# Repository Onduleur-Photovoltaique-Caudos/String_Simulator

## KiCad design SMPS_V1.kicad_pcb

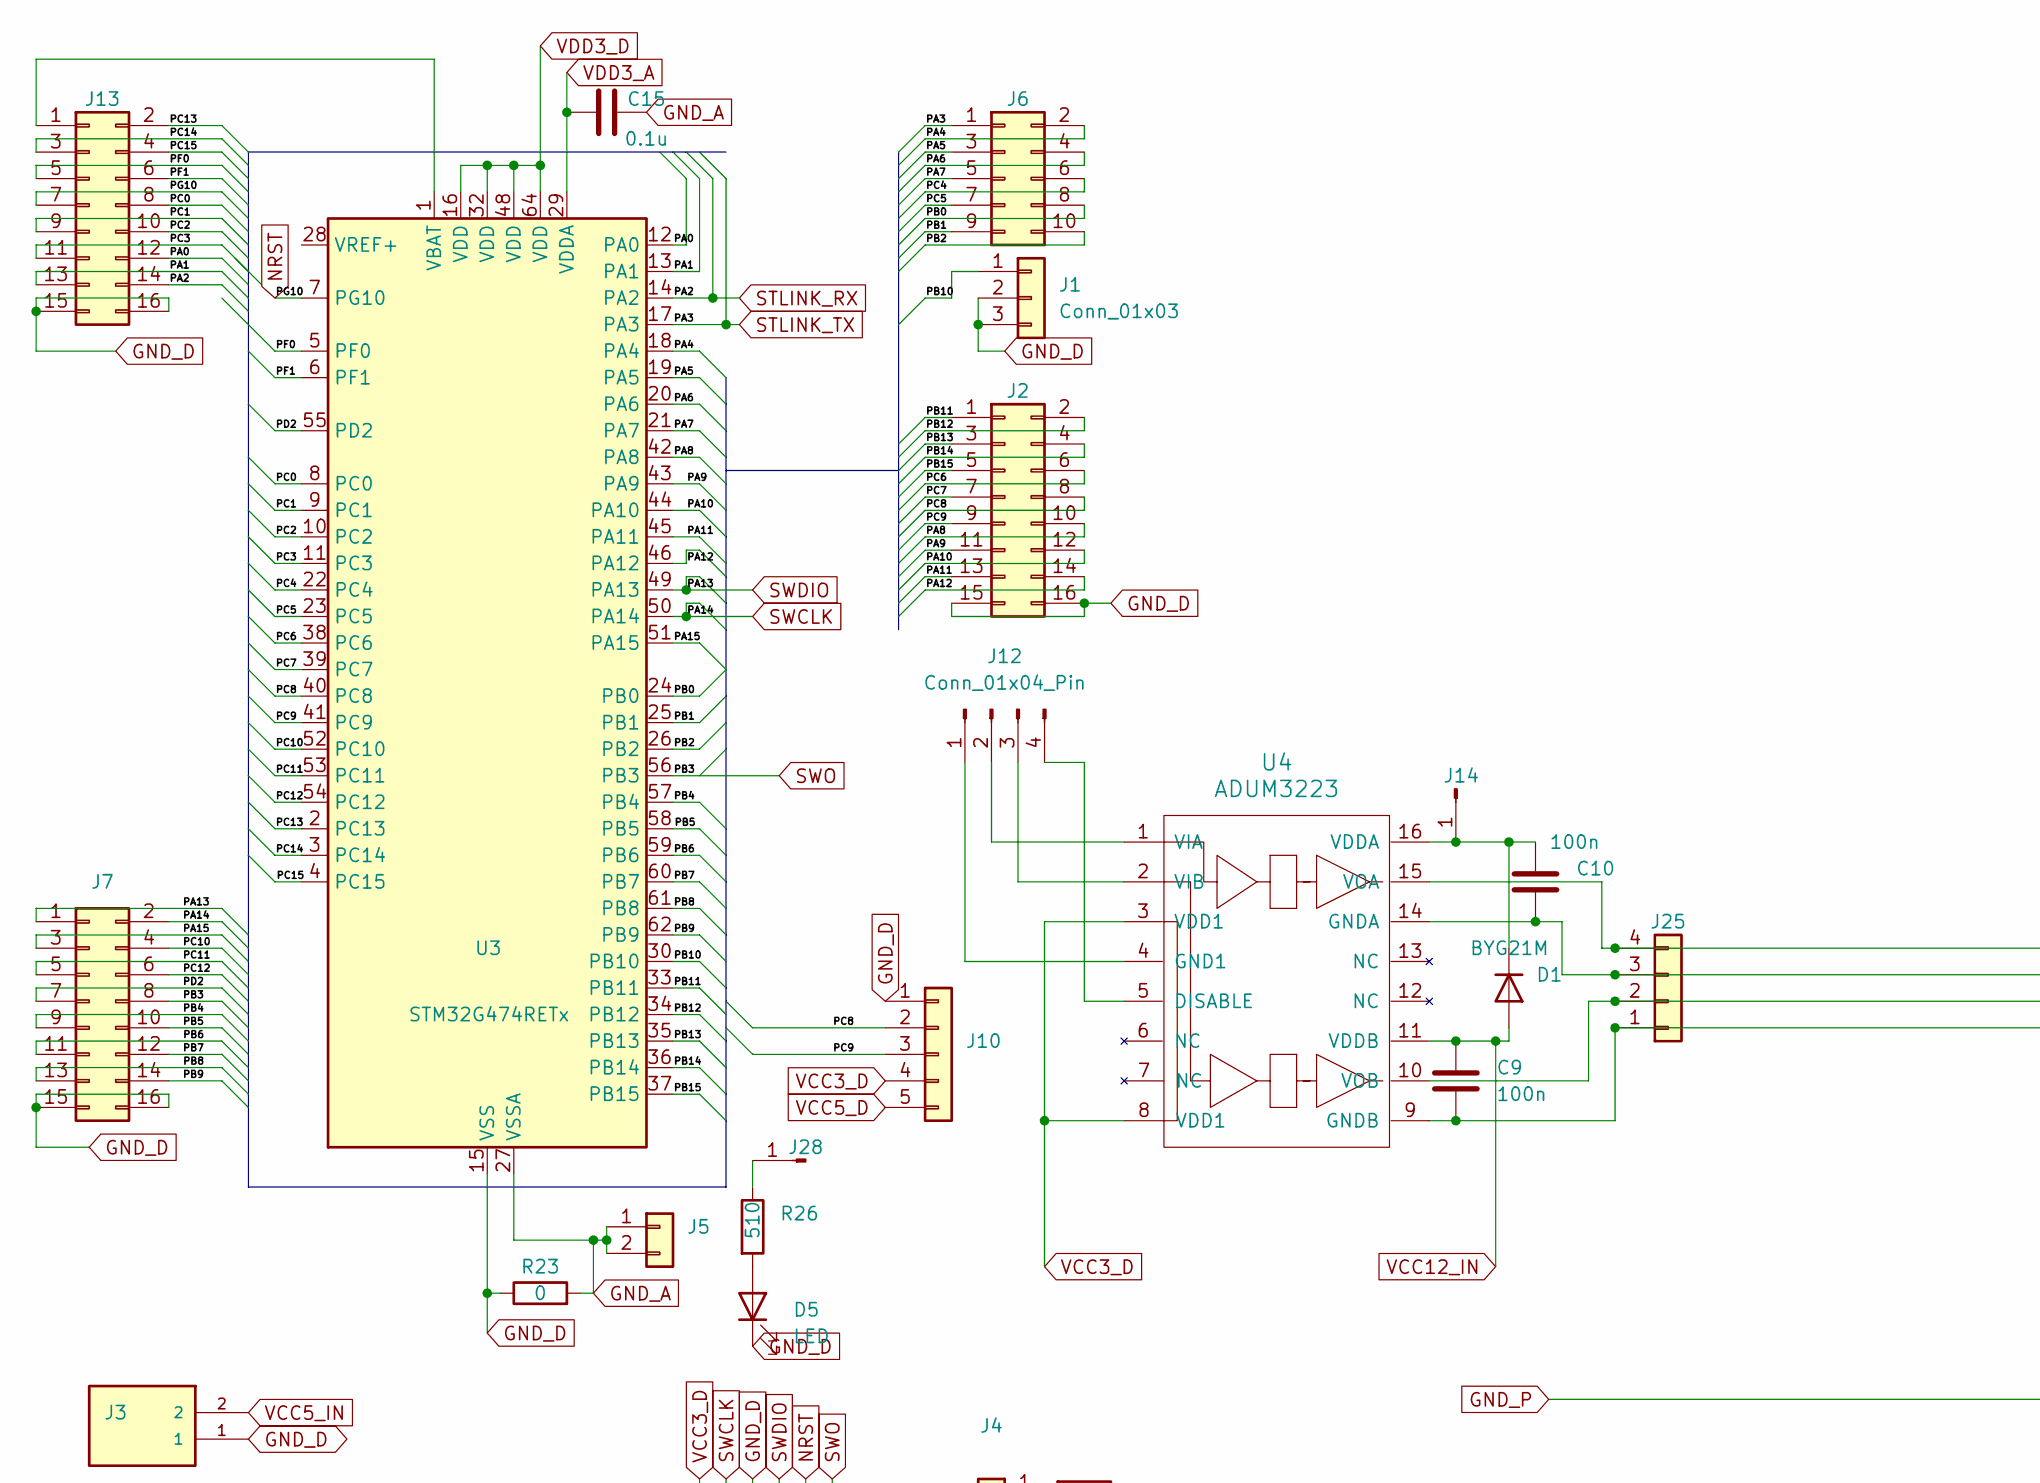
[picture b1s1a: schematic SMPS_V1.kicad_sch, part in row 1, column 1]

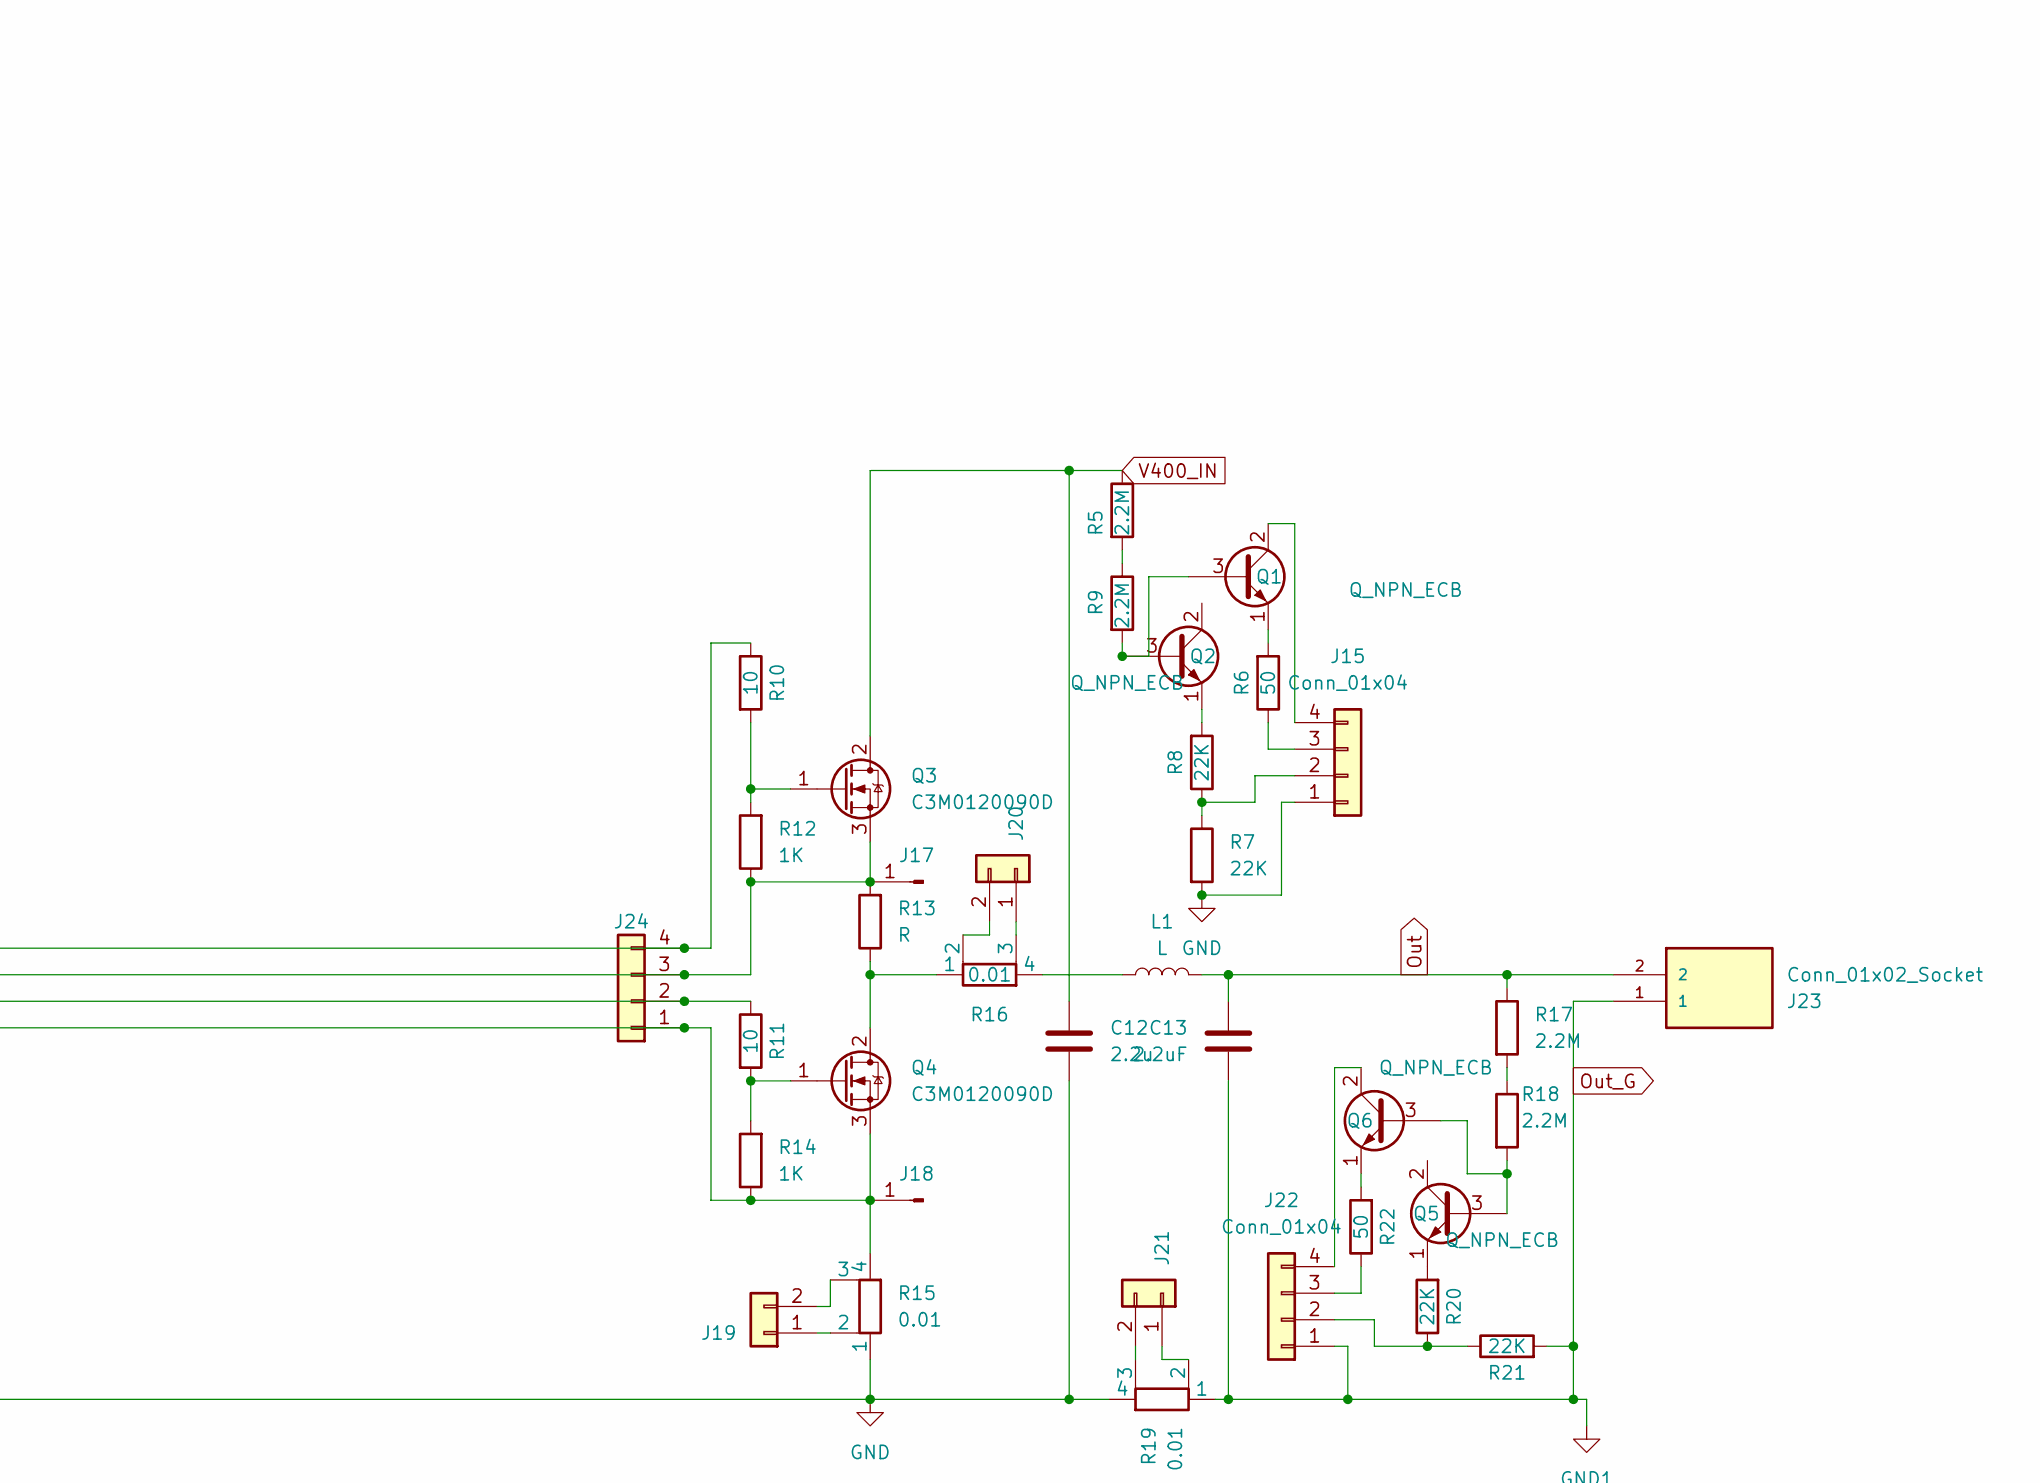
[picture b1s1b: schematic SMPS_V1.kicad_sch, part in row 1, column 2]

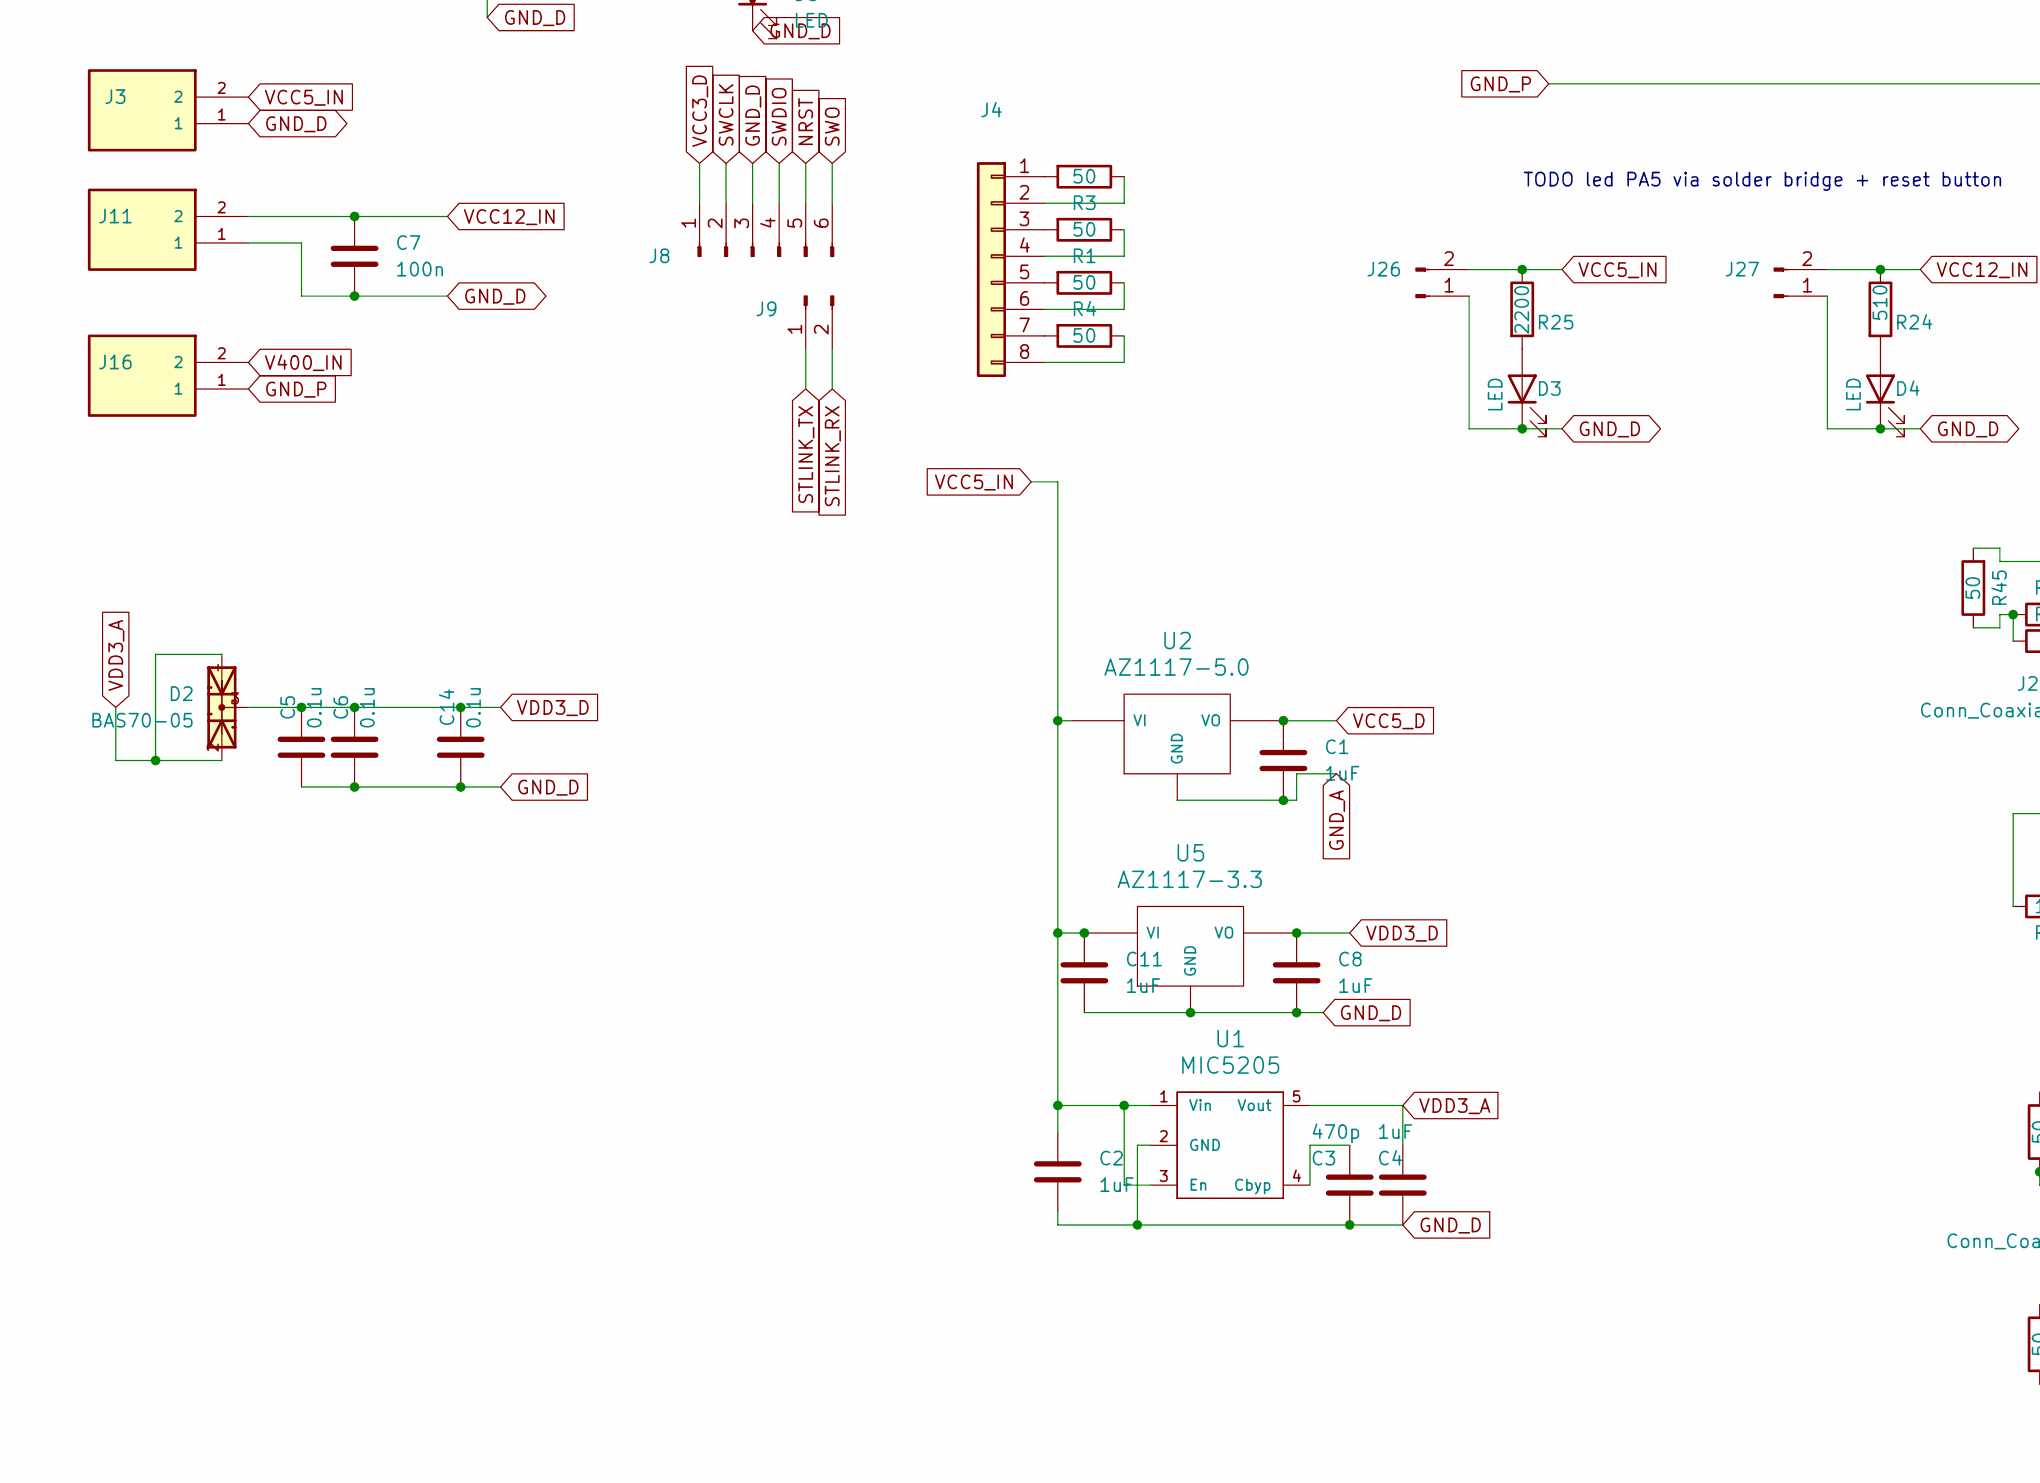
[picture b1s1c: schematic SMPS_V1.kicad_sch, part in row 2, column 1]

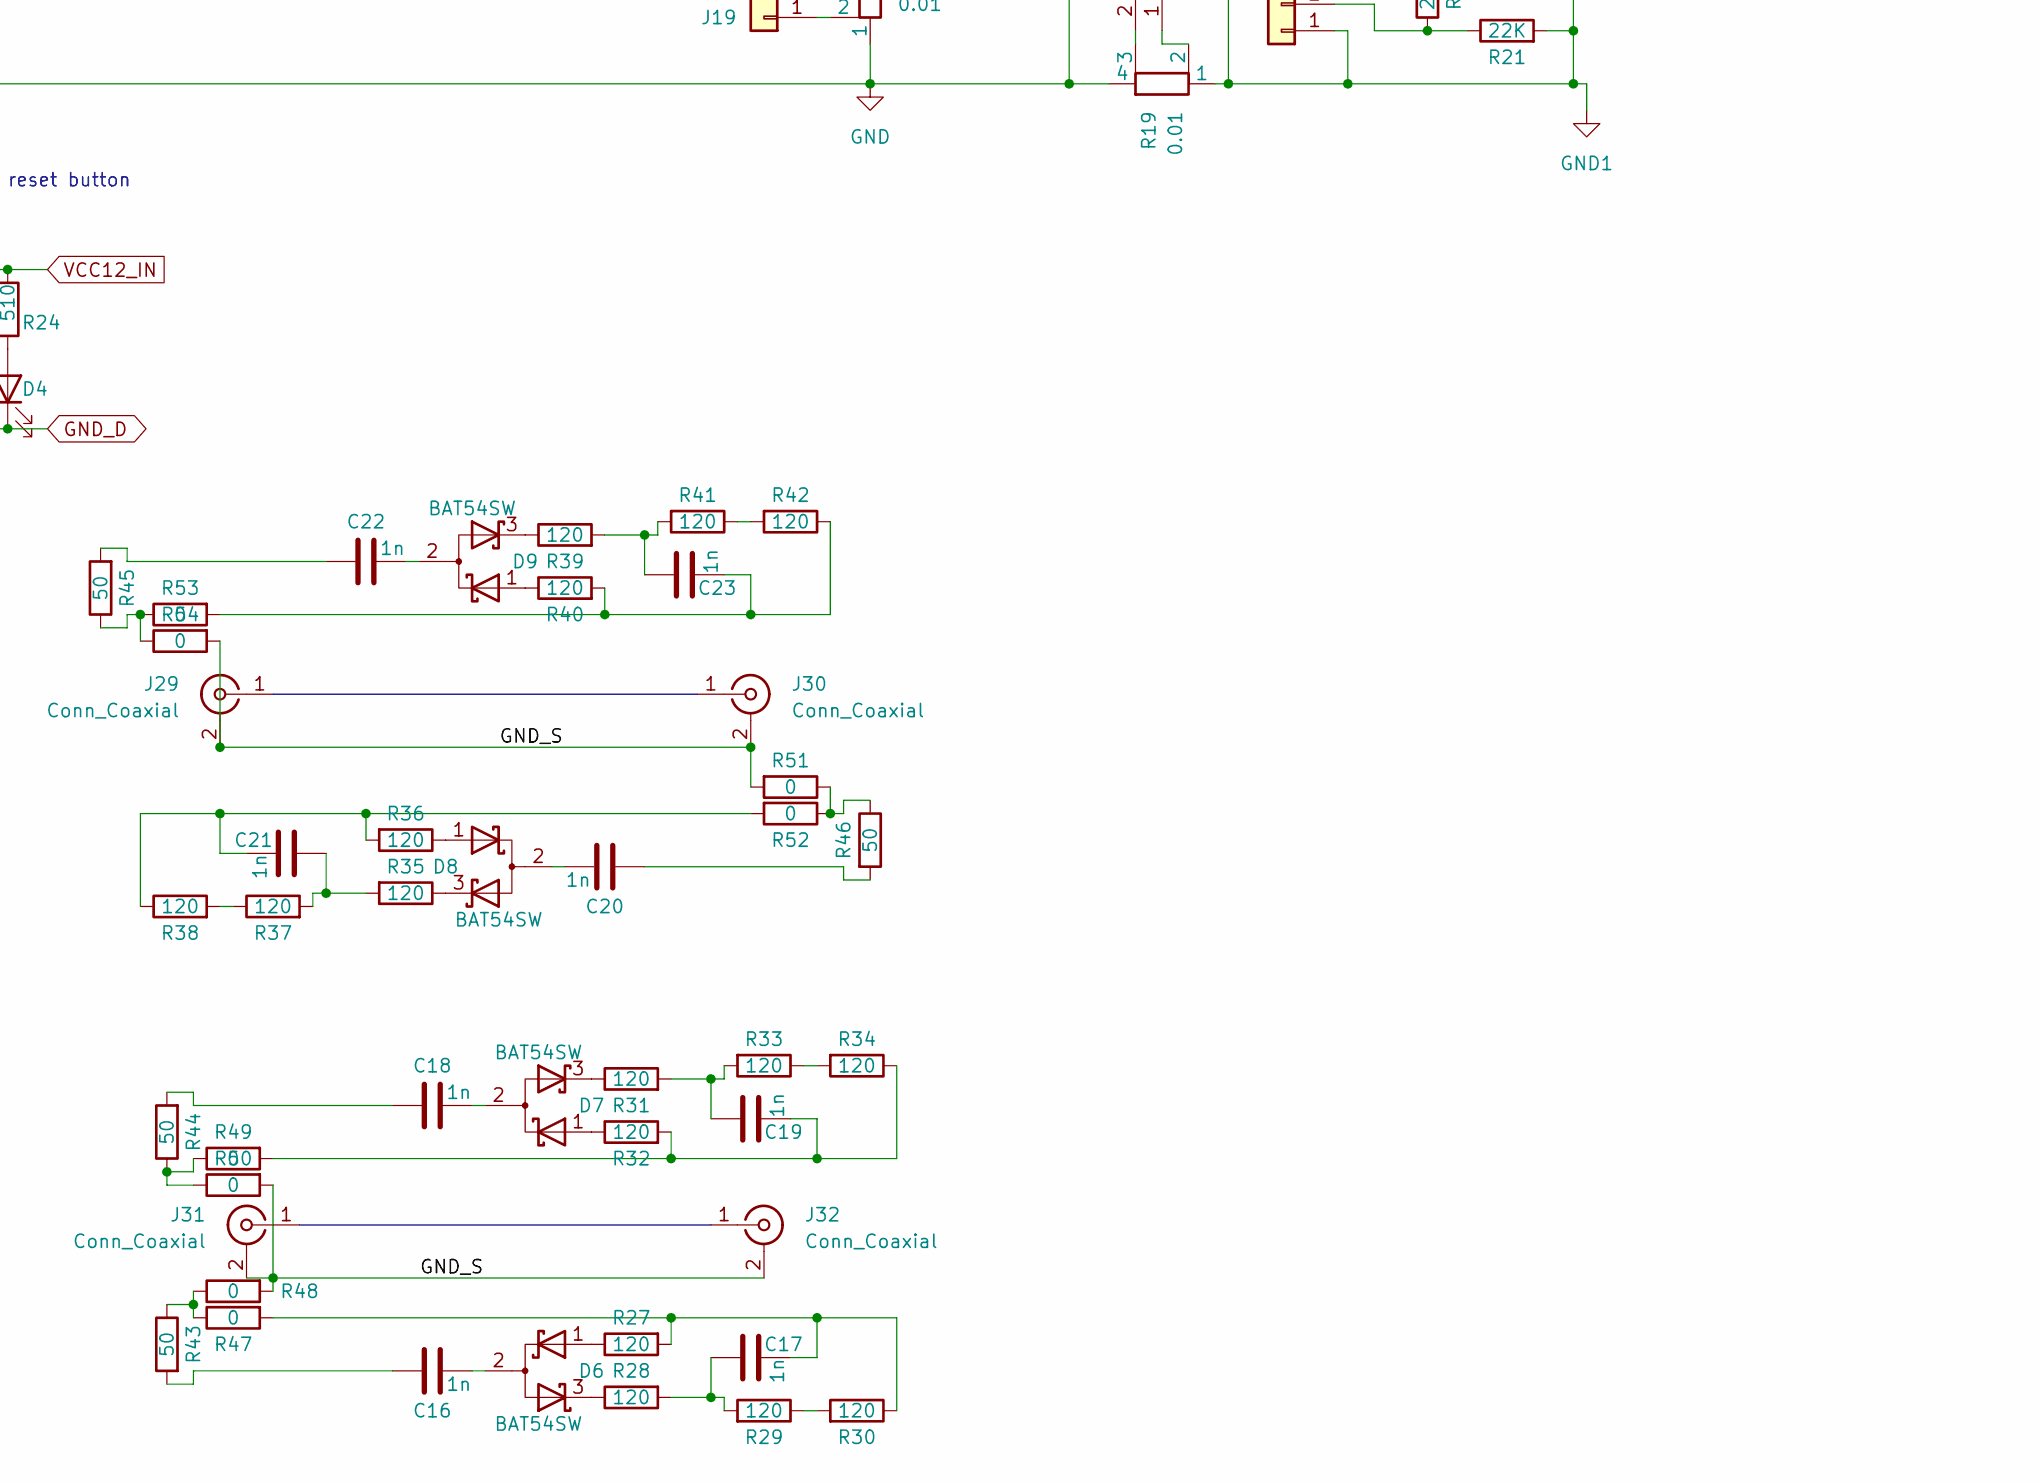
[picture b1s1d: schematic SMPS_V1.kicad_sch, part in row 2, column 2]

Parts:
C1: 1uF; LED_0805_2012Metric
C2, C4, C8, C11: 1uF; C_0603_1608Metric
C3: 470p; C_0603_1608Metric
C5, C6, C14, C15: 0.1u; C_0603_1608Metric
C7, C9, C10: 100n; C_1206_3216Metric
C12: 2.2u; C_Rect_W15_L32_P27.5
C13: 2.2uF; C_Rect_W15_L32_P27.5
C16, C17, C18, C19, C20, C21, C22, C23: 1n; C_0603_1608Metric
D1: BYG21M; DO-214-AC_SMA
D2: BAS70-05; SOT23
D3, D4, D5: LED; LED_0805_2012Metric
D6, D7, D8, D9: BAT54SW; SOT-23-D-PP
J1: Conn_01x03; PinHeader_1x03_P2.54mm_Vertical
J2, J7, J13: Conn_02x08_Odd_Even; PinHeader_2x08_P2.54mm_Vertical
J3, J11, J16, J23: Conn_01x02_Socket; CUI_TB004-508-P02BE
J4: Conn_01x08; PinHeader_1x08_P2.54mm_Vertical
J5, J19, J20, J21: Conn_01x02; PinHeader_1x02_P2.54mm_Vertical
J6: Conn_02x05_Odd_Even; PinHeader_2x05_P2.54mm_Vertical
J8: Conn_01x06_Pin; PinSocket_1x06_P2.54mm_Vertical
J9: Conn_01x02_Pin; PinSocket_1x02_P2.54mm_Vertical
J10: Conn_01x05; PinHeader_1x05_P2.54mm_Vertical
J12: Conn_01x04_Pin; PinHeader_1x04_P2.54mm_Vertical
J14, J17, J18, J28: Conn_01x01_Pin; PinHeader_1x01_P2.54mm_Vertical
J15, J22, J25: Conn_01x04; PinHeader_1x04_P2.54mm_Vertical
J24: Conn_01x04; PinSocket_1x04_P2.54mm_Vertical
J26, J27: Conn_01x02_Pin; PinHeader_1x02_P2.54mm_Vertical
J29, J30, J31, J32: Conn_Coaxial; SMA_Molex_73251-1153_EdgeMount_Horizontal
L1: L; Toroid-44-22
Q1, Q2, Q5, Q6: Q_NPN_ECB; SOT-23
Q3, Q4: C3M0120090D; TO-247-3_Vertical
R1, R2, R3, R4, R6, R22, R43, R44, R45, R46: 50; R_0603_1608Metric
R5, R9, R17, R18: 2.2M; R_1206_3216Metric_Pad1.30x1.75mm_HandSolder
R7, R8, R20, R21: 22K; R_0603_1608Metric
R10, R11: 10; R_0603_1608Metric
R12, R14: 1K; R_0603_1608Metric
R13: R; R_Axial_DIN0614_L14.3mm_D5.7mm_P15.24mm_Horizontal
R15, R16, R19: 0.01; R_Shunt_Axial_DIN0414_L11.9mm_D4.5mm_P15.24mm_Horizontal
R23, R47, R48, R49, R50, R51, R52, R53, R54: 0; R_0603_1608Metric
R24, R26: 510; R_0603_1608Metric
R25: 2200; R_0603_1608Metric
R27, R28, R29, R30, R31, R32, R33, R34, R35, R36, R37, R38, R39, R40, R41, R42: 120; R_0603_1608Metric
U1: MIC5205; SOT23-5
U2: AZ1117-5.0; SOT-223
U3: STM32G474RETx; LQFP-64_10x10mm_P0.5mm
U4: ADUM3223; SOIC-16_3.9x9.9mm_P1.27mm
U5: AZ1117-3.3; SOT-223

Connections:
/GND_S: J29.2 (Ext), J30.2 (Ext), J31.2 (Ext), J32.2 (Ext), R48.2, R50.2, R51.2, R54.2
/PA0: J13.12, U3.12 (PA0)
/PA1: J13.13, U3.13 (PA1)
/PA4: J6.2, U3.18 (PA4)
/PA5: J6.3, U3.19 (PA5)
/PA6: J6.4, U3.20 (PA6)
/PA7: J6.5, U3.21 (PA7)
/PA8: J2.10, U3.42 (PA8)
/PA9: J2.11, U3.43 (PA9)
/PA10: J2.12, U3.44 (PA10)
/PA11: J2.13, U3.45 (PA11)
/PA12: J2.14, U3.46 (PA12)
/PA15: J7.3, U3.51 (PA15)
/PB0: J6.8, U3.24 (PB0)
/PB1: J6.9, U3.25 (PB1)
/PB2: J6.10, U3.26 (PB2)
/PB4: J7.9, U3.57 (PB4)
/PB5: J7.10, U3.58 (PB5)
/PB6: J7.11, U3.59 (PB6)
/PB7: J7.12, U3.60 (PB7)
/PB8: J7.13, U3.61 (PB8)
/PB9: J7.14, U3.62 (PB9)
/PB10: J1.1, U3.30 (PB10)
/PB11: J2.1, U3.33 (PB11)
/PB12: J2.2, U3.34 (PB12)
/PB13: J2.3, U3.35 (PB13)
/PB14: J2.4, U3.36 (PB14)
/PB15: J2.5, U3.37 (PB15)
/PC0: J13.8, U3.8 (PC0)
/PC1: J13.9, U3.9 (PC1)
/PC2: J13.10, U3.10 (PC2)
/PC3: J13.11, U3.11 (PC3)
/PC4: J6.6, U3.22 (PC4)
/PC5: J6.7, U3.23 (PC5)
/PC6: J2.6, U3.38 (PC6)
/PC7: J2.7, U3.39 (PC7)
/PC8: J2.8, J10.2, U3.40 (PC8)
/PC9: J2.9, J10.3, U3.41 (PC9)
/PC10: J7.4, U3.52 (PC10)
/PC11: J7.5, U3.53 (PC11)
/PC12: J7.6, U3.54 (PC12)
/PC13: J13.2, U3.2 (PC13)
/PC14: J13.3, U3.3 (PC14)
/PC15: J13.4, U3.4 (PC15)
/PD2: J7.7, U3.55 (PD2)
/PF0: J13.5, U3.5 (PF0)
/PF1: J13.6, U3.6 (PF1)
GND_A: C1.2, C15.2, J5.1, J5.2, R23.2, U2.1 (GND), U3.27 (VSSA)
GND_D: C2.2, C3.2, C4.2, C5.1, C6.1, C7.2, C8.2, C11.2, C14.1, D3.1 (K), D4.1 (K), D5.1 (K), J1.2, J1.3, J2.15, J2.16, J3.1, J7.15, J7.16, J8.3, J10.1, J11.1, J13.15, J13.16, J26.1, J27.1, R23.1, U1.2 (GND), U3.15 (VSS), U3.31 (VSS), U3.47 (VSS), U3.63 (VSS), U5.1 (GND)
GND_P: C12.2, J15.1, J16.1, R7.2, R15.1, R19.4
NRST: J8.5, J13.7, U3.7 (PG10)
unnamed: C16.1, R43.2
unnamed: C17.1, R27.2, R30.1, R47.2
unnamed: C17.2, R28.2, R29.2
unnamed: C18.1, R44.2
unnamed: C19.1, R32.2, R34.1, R49.2
unnamed: C19.2, R31.2, R33.2
unnamed: C20.1, R46.2
unnamed: C21.1, R36.2, R38.1, R52.2
unnamed: C21.2, R35.2, R37.2
unnamed: C22.1, R45.2
unnamed: C23.1, R40.2, R42.1, R53.2
unnamed: C23.2, R39.2, R41.2
unnamed: C10.1, D1.1 (K), J14.1, U4.16 (VDDA)
unnamed: D3.2 (A), R25.2
unnamed: D4.2 (A), R24.2
unnamed: D5.2 (A), R26.2
unnamed: C16.2, D6.2 (A)
unnamed: D6.1 (K), R27.1
unnamed: D6.3 (K), R28.1
unnamed: C18.2, D7.2 (A)
unnamed: D7.1 (K), R32.1
unnamed: D7.3 (K), R31.1
unnamed: C20.2, D8.2 (A)
unnamed: D8.1 (K), R36.1
unnamed: D8.3 (K), R35.1
unnamed: C22.2, D9.2 (A)
unnamed: D9.1 (K), R40.1
unnamed: D9.3 (K), R39.1
unnamed: J4.1, R2.2
unnamed: J4.2, R2.1
unnamed: J4.3, R3.2
unnamed: J4.4, R3.1
unnamed: J4.5, R1.2
unnamed: J4.6, R1.1
unnamed: J4.7, R4.2
unnamed: J4.8, R4.1
unnamed: J12.1, U4.4 (GND1)
unnamed: J12.2, U4.1 (VIA)
unnamed: J12.3, U4.2 (VIB)
unnamed: J12.4, U4.5 (DISABLE)
unnamed: J13.1, U3.1 (VBAT)
unnamed: J15.2, R7.1, R8.1
unnamed: J15.3, R6.1
unnamed: J15.4, Q1.2 (C)
unnamed: C10.2, J17.1, J24.3, J25.3, Q3.3 (S), R12.1, R13.2, U4.14 (GNDA)
unnamed: C9.2, J18.1, J24.1, J25.1, Q4.3 (S), R14.1, R15.4, U4.9 (GNDB)
unnamed: J19.1, R15.2
unnamed: J19.2, R15.3
unnamed: J20.1, R16.3
unnamed: J20.2, R16.2
unnamed: J21.1, R19.2
unnamed: J21.2, R19.3
unnamed: J22.2, R20.1, R21.1
unnamed: J22.3, R22.1
unnamed: J22.4, Q6.2 (C)
unnamed: J24.2, J25.2, R11.1, U4.10 (VOB)
unnamed: J24.4, J25.4, R10.1, U4.15 (VOA)
unnamed: J28.1, R26.1
unnamed: J29.1 (In), J30.1 (In)
unnamed: J31.1 (In), J32.1 (In)
unnamed: L1.1, R16.4
unnamed: Q1.3 (B), Q2.3 (B), R9.2
unnamed: Q1.1 (E), R6.2
unnamed: Q2.1 (E), R8.2
unnamed: Q3.1 (G), R10.2, R12.2
unnamed: Q4.2 (D), R13.1, R16.1
unnamed: Q4.1 (G), R11.2, R14.2
unnamed: Q5.3 (B), Q6.3 (B), R18.2
unnamed: Q5.1 (E), R20.2
unnamed: Q6.1 (E), R22.2
unnamed: R5.2, R9.1
unnamed: R17.2, R18.1
unnamed: R29.1, R30.2
unnamed: R33.1, R34.2
unnamed: R37.1, R38.2
unnamed: R41.1, R42.2
unnamed: R43.1, R47.1, R48.1
unnamed: R44.1, R49.1, R50.1
unnamed: R45.1, R53.1, R54.1
unnamed: R46.1, R51.1, R52.1
unnamed: C3.1, U1.4 (Cbyp)
Out: C13.1, J23.2, L1.2, R17.1
Out_G: C13.2, J22.1, J23.1, R19.1, R21.2
STLINK_RX: J9.2, J13.14, U3.14 (PA2)
STLINK_TX: J6.1, J9.1, U3.17 (PA3)
SWCLK: J7.2, J8.2, U3.50 (PA14)
SWDIO: J7.1, J8.4, U3.49 (PA13)
SWO: J7.8, J8.6, U3.56 (PB3)
V400_IN: C12.1, J16.2, Q3.2 (D), R5.1
VCC3_D: J8.1, J10.4, U4.3 (VDD1), U4.8 (VDD1)
VCC5_D: C1.1, J10.5, U2.2 (VO)
VCC5_IN: C2.1, C11.1, J3.2, J26.2, R25.1, U1.1 (Vin), U1.3 (En), U2.3 (VI), U5.3 (VI)
VCC12_IN: C7.1, C9.1, D1.2 (A), J11.2, J27.2, R24.1, U4.11 (VDDB)
VDD3_A: C4.1, C15.1, D2.1, D2.2, U1.5 (Vout), U3.29 (VDDA)
VDD3_D: C5.2, C6.2, C8.1, C14.2, D2.3, U3.16 (VDD), U3.32 (VDD), U3.48 (VDD), U3.64 (VDD), U5.2 (VO)

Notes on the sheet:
TODO led PA5 via solder bridge + reset button

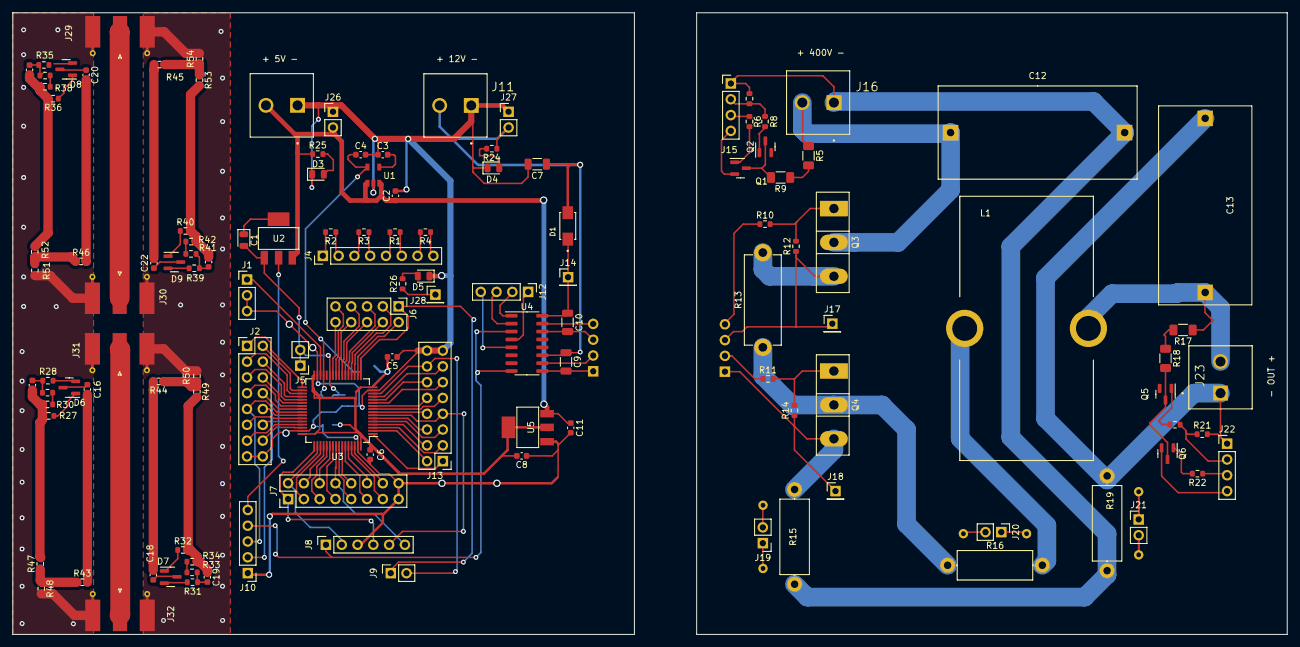
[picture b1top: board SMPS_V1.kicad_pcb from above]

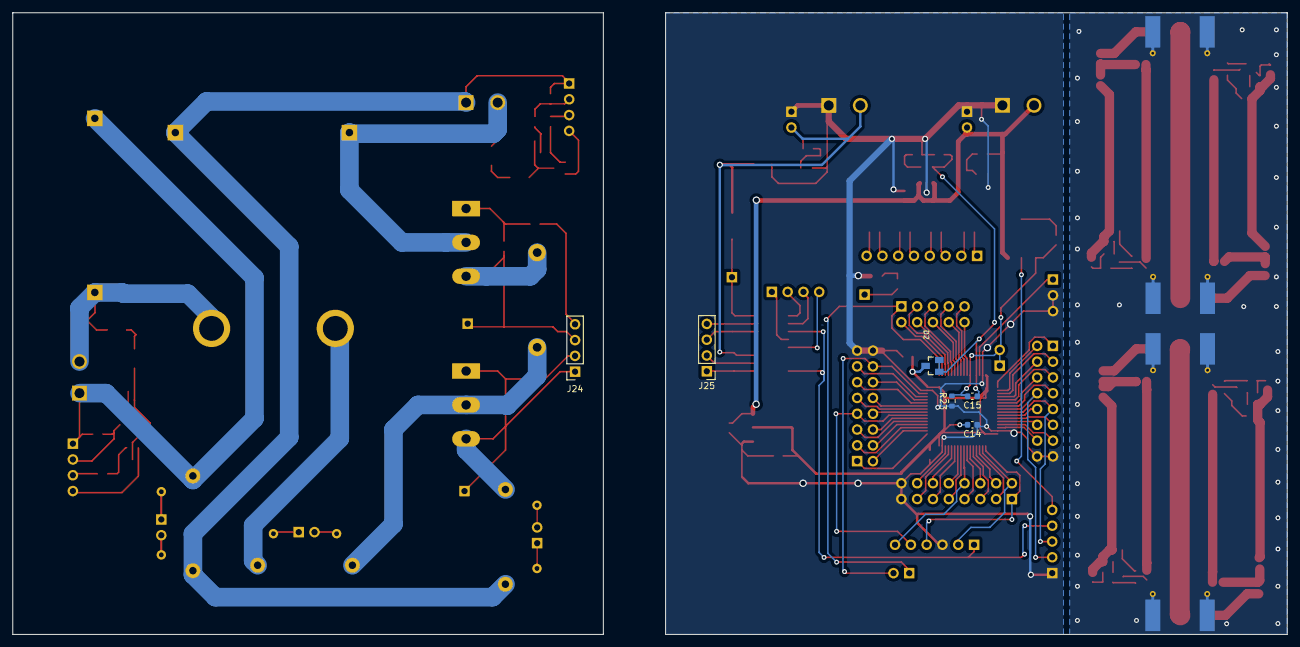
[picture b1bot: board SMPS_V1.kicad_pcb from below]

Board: 2 copper layers, 205.0 x 100.0 mm, 130 parts (6 on the bottom side), 146 nets.

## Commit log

2023-12-08 initial commit envoi chez Elecrow
